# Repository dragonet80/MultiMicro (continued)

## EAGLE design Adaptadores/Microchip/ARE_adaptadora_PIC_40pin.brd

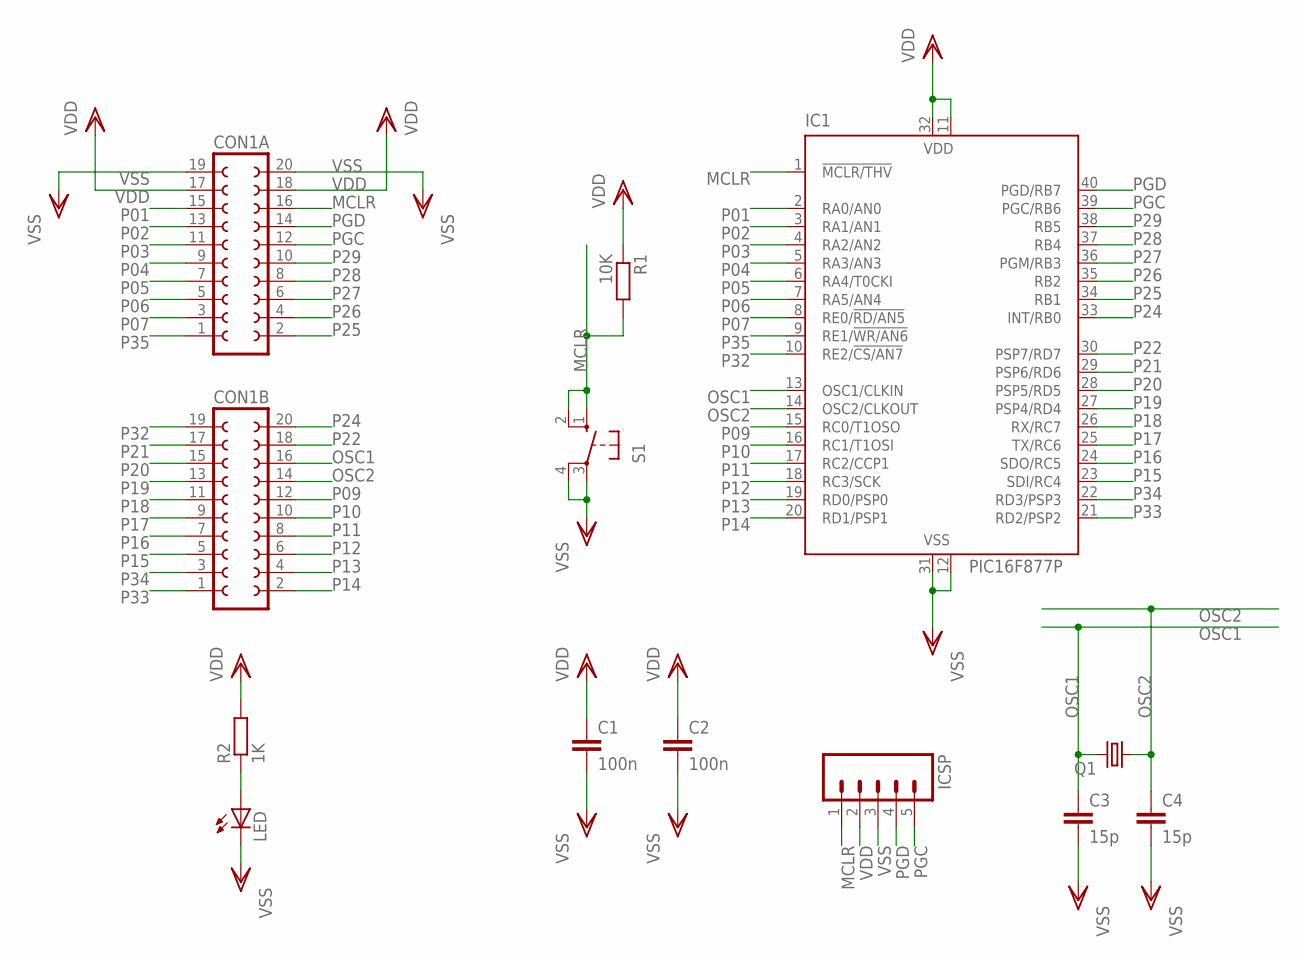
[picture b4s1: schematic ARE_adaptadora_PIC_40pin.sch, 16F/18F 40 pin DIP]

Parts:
C1, C2: 100n; C0805
C3, C4: 15p; C0805
CON1A, CON1B: FE10-2W
IC1: PIC16F877P; DIL40
ICSP: M05PTH; 1X05
LED: LED3MM
Q1: CRYSTALHC18U-V; HC18U-V
R1: 10K; R0805
R2: 1K; R0805
S1: 10-XX; B3F-10XX; MPN B3F-1000

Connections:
MCLR: CON1A.16, IC1.1 (!MCLR/THV), ICSP.1, R1.2, S1.1 (S), S1.2 (S1)
unnamed: LED.A, R2.1
OSC1: C3.1, CON1B.16, IC1.13 (OSC1/CLKIN), Q1.2
OSC2: C4.1, CON1B.14, IC1.14 (OSC2/CLKOUT), Q1.1
P01: CON1A.15, IC1.2 (RA0/AN0)
P02: CON1A.13, IC1.3 (RA1/AN1)
P03: CON1A.11, IC1.4 (RA2/AN2)
P04: CON1A.9, IC1.5 (RA3/AN3)
P05: CON1A.7, IC1.6 (RA4/T0CKI)
P06: CON1A.5, IC1.7 (RA5/AN4)
P07: CON1A.3, IC1.8 (RE0/!RD/AN5)
P09: CON1B.12, IC1.15 (RC0/T1OSO)
P10: CON1B.10, IC1.16 (RC1/T1OSI)
P11: CON1B.8, IC1.17 (RC2/CCP1)
P12: CON1B.6, IC1.18 (RC3/SCK)
P13: CON1B.4, IC1.19 (RD0/PSP0)
P14: CON1B.2, IC1.20 (RD1/PSP1)
P15: CON1B.5, IC1.23 (SDI/RC4)
P16: CON1B.7, IC1.24 (SDO/RC5)
P17: CON1B.9, IC1.25 (TX/RC6)
P18: CON1B.11, IC1.26 (RX/RC7)
P19: CON1B.13, IC1.27 (PSP4/RD4)
P20: CON1B.15, IC1.28 (PSP5/RD5)
P21: CON1B.17, IC1.29 (PSP6/RD6)
P22: CON1B.18, IC1.30 (PSP7/RD7)
P24: CON1B.20, IC1.33 (INT/RB0)
P25: CON1A.2, IC1.34 (RB1)
P26: CON1A.4, IC1.35 (RB2)
P27: CON1A.6, IC1.36 (PGM/RB3)
P28: CON1A.8, IC1.37 (RB4)
P29: CON1A.10, IC1.38 (RB5)
P32: CON1B.19, IC1.10 (RE2/!CS/AN7)
P33: CON1B.1, IC1.21 (RD2/PSP2)
P34: CON1B.3, IC1.22 (RD3/PSP3)
P35: CON1A.1, IC1.9 (RE1/!WR/AN6)
PGC: CON1A.12, IC1.39 (PGC/RB6), ICSP.5
PGD: CON1A.14, IC1.40 (PGD/RB7), ICSP.4
VDD: C1.1, C2.1, CON1A.17, CON1A.18, IC1.11 (VDD), IC1.32 (VDD), ICSP.2, R1.1, R2.2
VSS: C1.2, C2.2, C3.2, C4.2, CON1A.19, CON1A.20, IC1.12 (VSS), IC1.31 (VSS), ICSP.3, LED.K (C), S1.3, S1.4 (P1)

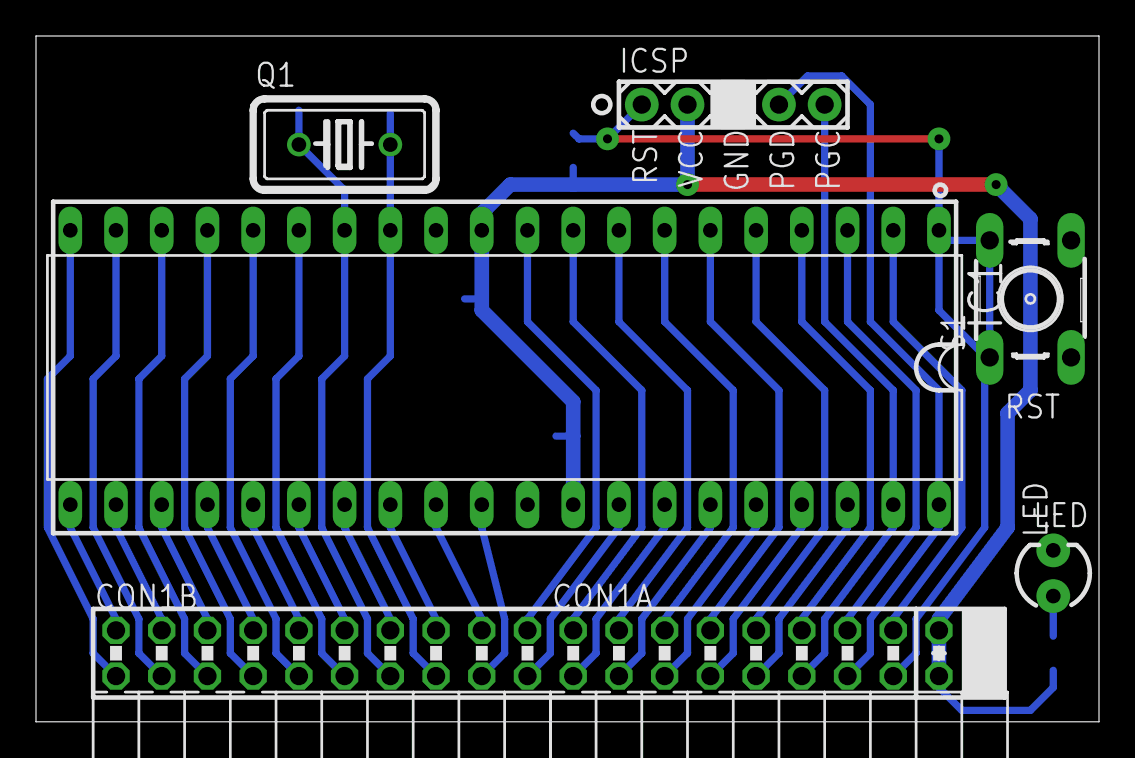
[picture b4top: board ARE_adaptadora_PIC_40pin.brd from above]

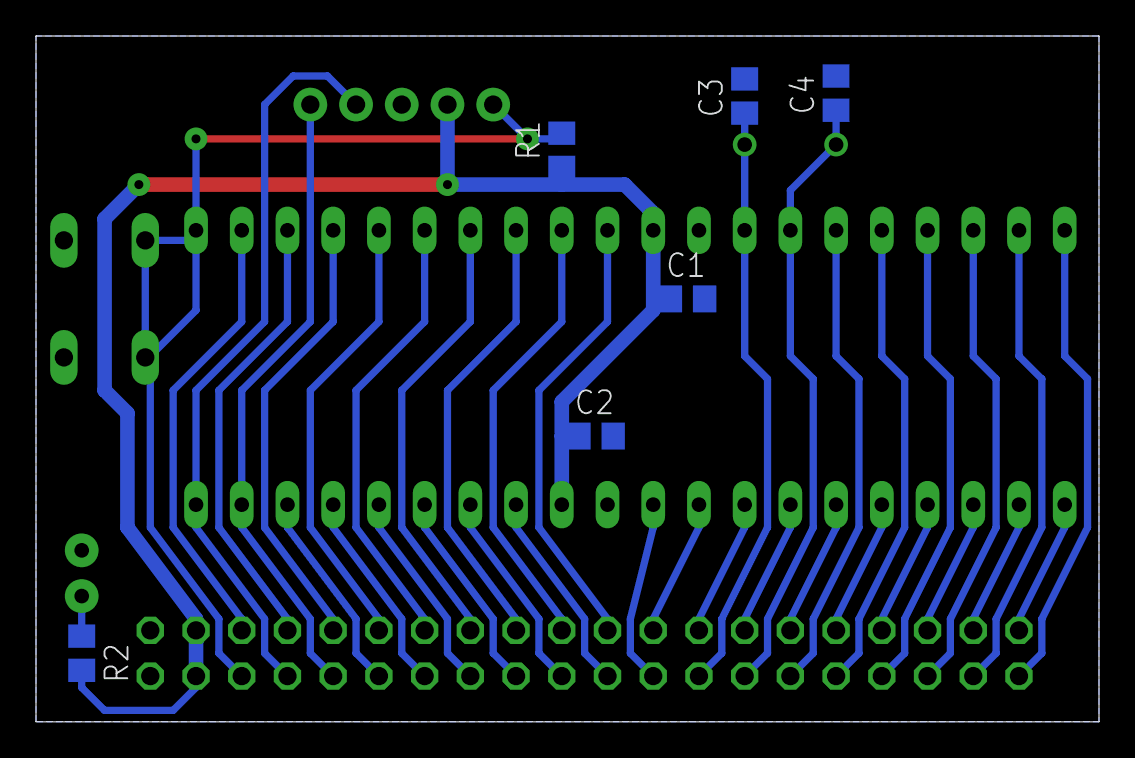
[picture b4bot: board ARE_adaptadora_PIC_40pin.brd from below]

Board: 2 copper layers, 59.1 x 38.1 mm, 13 parts (6 on the bottom side), 39 nets.

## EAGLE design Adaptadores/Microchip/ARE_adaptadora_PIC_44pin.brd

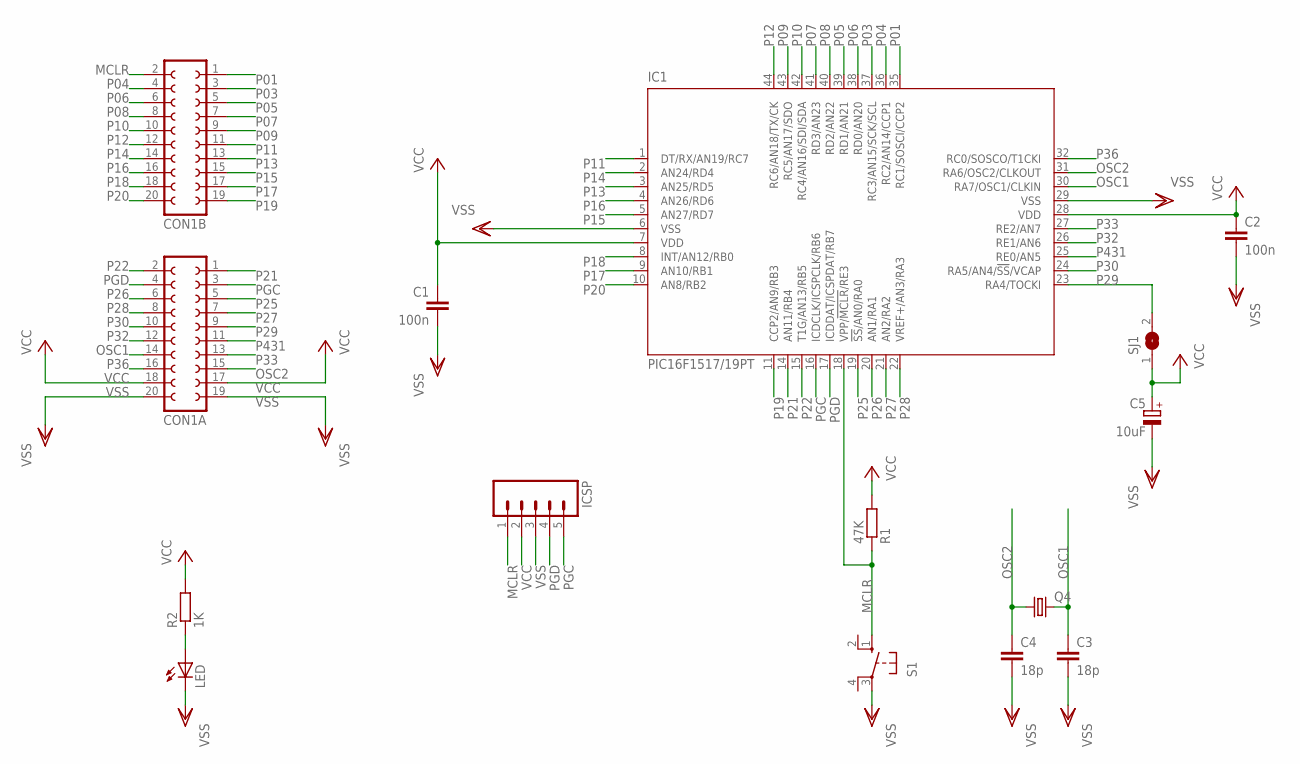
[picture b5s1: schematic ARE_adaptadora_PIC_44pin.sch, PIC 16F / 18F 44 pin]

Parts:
C1, C2: 100n; C0805
C3, C4: 18p; C0805
C5: 10uF; SMC_C
CON1A, CON1B: FE10-2W
IC1: PIC16F1517/19PT; TQFP44
ICSP: M05PTH; 1X05
LED: LEDCHIPLED_0805; CHIPLED_0805
Q4: CRYSTALHC18U-V; HC18U-V
R1: 47K; R0805
R2: 1K; R0805
S1: 10-XX; B3F-10XX; MPN B3F-1000
SJ1: SJ

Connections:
MCLR: CON1B.2, IC1.18 (VPP/!MCLR!/RE3), ICSP.1, R1.1, S1.1 (S)
unnamed: LED.A, R2.1
OSC1: C3.1, CON1A.14, IC1.30 (RA7/OSC1/CLKIN), Q4.2
OSC2: C4.1, CON1A.15, IC1.31 (RA6/OSC2/CLKOUT), Q4.1
P01: CON1B.1, IC1.35 (RC1/SOSCI/CCP2)
P03: CON1B.3, IC1.37 (RC3/AN15/SCK/SCL)
P04: CON1B.4, IC1.36 (RC2/AN14/CCP1)
P05: CON1B.5, IC1.39 (RD1/AN21)
P06: CON1B.6, IC1.38 (RD0/AN20)
P07: CON1B.7, IC1.41 (RD3/AN23)
P08: CON1B.8, IC1.40 (RD2/AN22)
P09: CON1B.9, IC1.43 (RC5/AN17/SDO)
P10: CON1B.10, IC1.42 (RC4/AN16/SDI/SDA)
P11: CON1B.11, IC1.1 (DT/RX/AN19/RC7)
P12: CON1B.12, IC1.44 (RC6/AN18/TX/CK)
P13: CON1B.13, IC1.3 (AN25/RD5)
P14: CON1B.14, IC1.2 (AN24/RD4)
P15: CON1B.15, IC1.5 (AN27/RD7)
P16: CON1B.16, IC1.4 (AN26/RD6)
P17: CON1B.17, IC1.9 (AN10/RB1)
P18: CON1B.18, IC1.8 (INT/AN12/RB0)
P19: CON1B.19, IC1.11 (CCP2/AN9/RB3)
P20: CON1B.20, IC1.10 (AN8/RB2)
P21: CON1A.1, IC1.14 (AN11/RB4)
P22: CON1A.2, IC1.15 (T1G/AN13/RB5)
P25: CON1A.5, IC1.19 (!SS!/AN0/RA0)
P26: CON1A.6, IC1.20 (AN1/RA1)
P27: CON1A.7, IC1.21 (AN2/RA2)
P28: CON1A.8, IC1.22 (VREF+/AN3/RA3)
P29: CON1A.9, IC1.23 (RA4/TOCKI), SJ1.2
P30: CON1A.10, IC1.24 (RA5/AN4/!SS!/VCAP)
P32: CON1A.12, IC1.26 (RE1/AN6)
P33: CON1A.13, IC1.27 (RE2/AN7)
P36: CON1A.16, IC1.32 (RC0/SOSCO/T1CKI)
P431: CON1A.11, IC1.25 (RE0/AN5)
PGC: CON1A.3, IC1.16 (ICDCLK/ICSPCLK/RB6), ICSP.5
PGD: CON1A.4, IC1.17 (ICDDAT/ICSPDAT/RB7), ICSP.4
VCC: C1.1, C2.1, C5.+, CON1A.17, CON1A.18, IC1.7 (VDD), IC1.28 (VDD), ICSP.2, R1.2, R2.2, SJ1.1
VSS: C1.2, C2.2, C3.2, C4.2, C5.-, CON1A.19, CON1A.20, IC1.6 (VSS), IC1.29 (VSS), ICSP.3, LED.C, S1.3

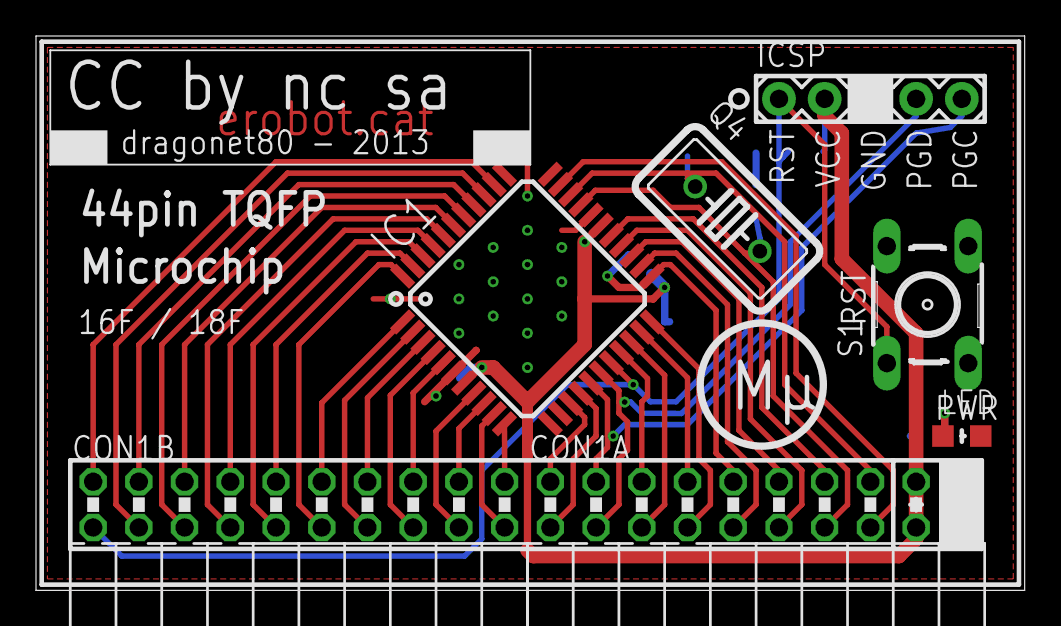
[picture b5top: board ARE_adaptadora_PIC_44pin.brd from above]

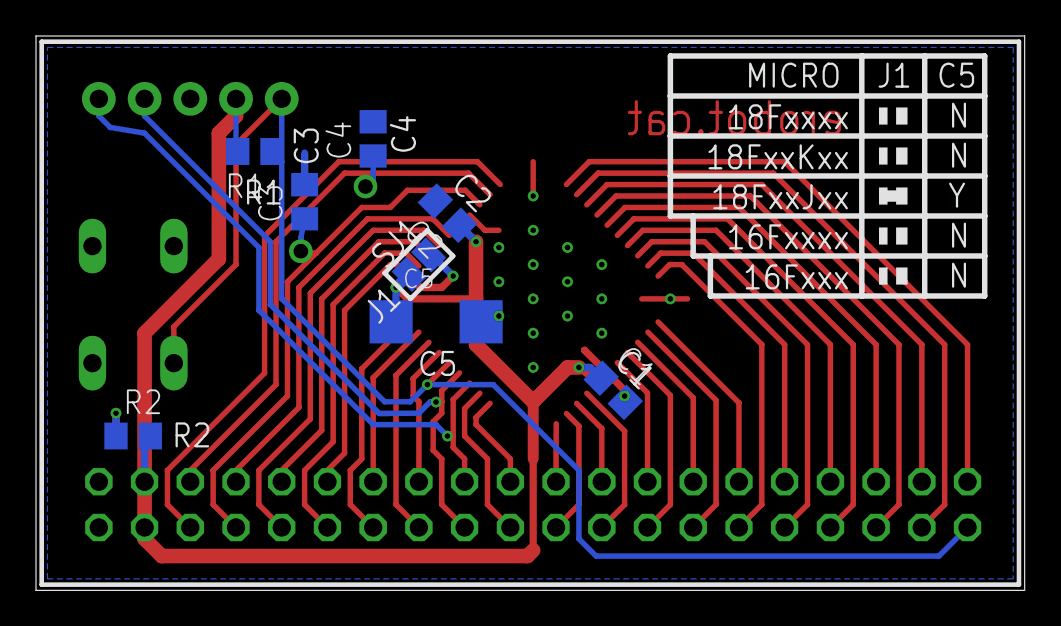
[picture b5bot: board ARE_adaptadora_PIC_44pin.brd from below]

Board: 2 copper layers, 54.9 x 30.8 mm, 15 parts (8 on the bottom side), 39 nets.
